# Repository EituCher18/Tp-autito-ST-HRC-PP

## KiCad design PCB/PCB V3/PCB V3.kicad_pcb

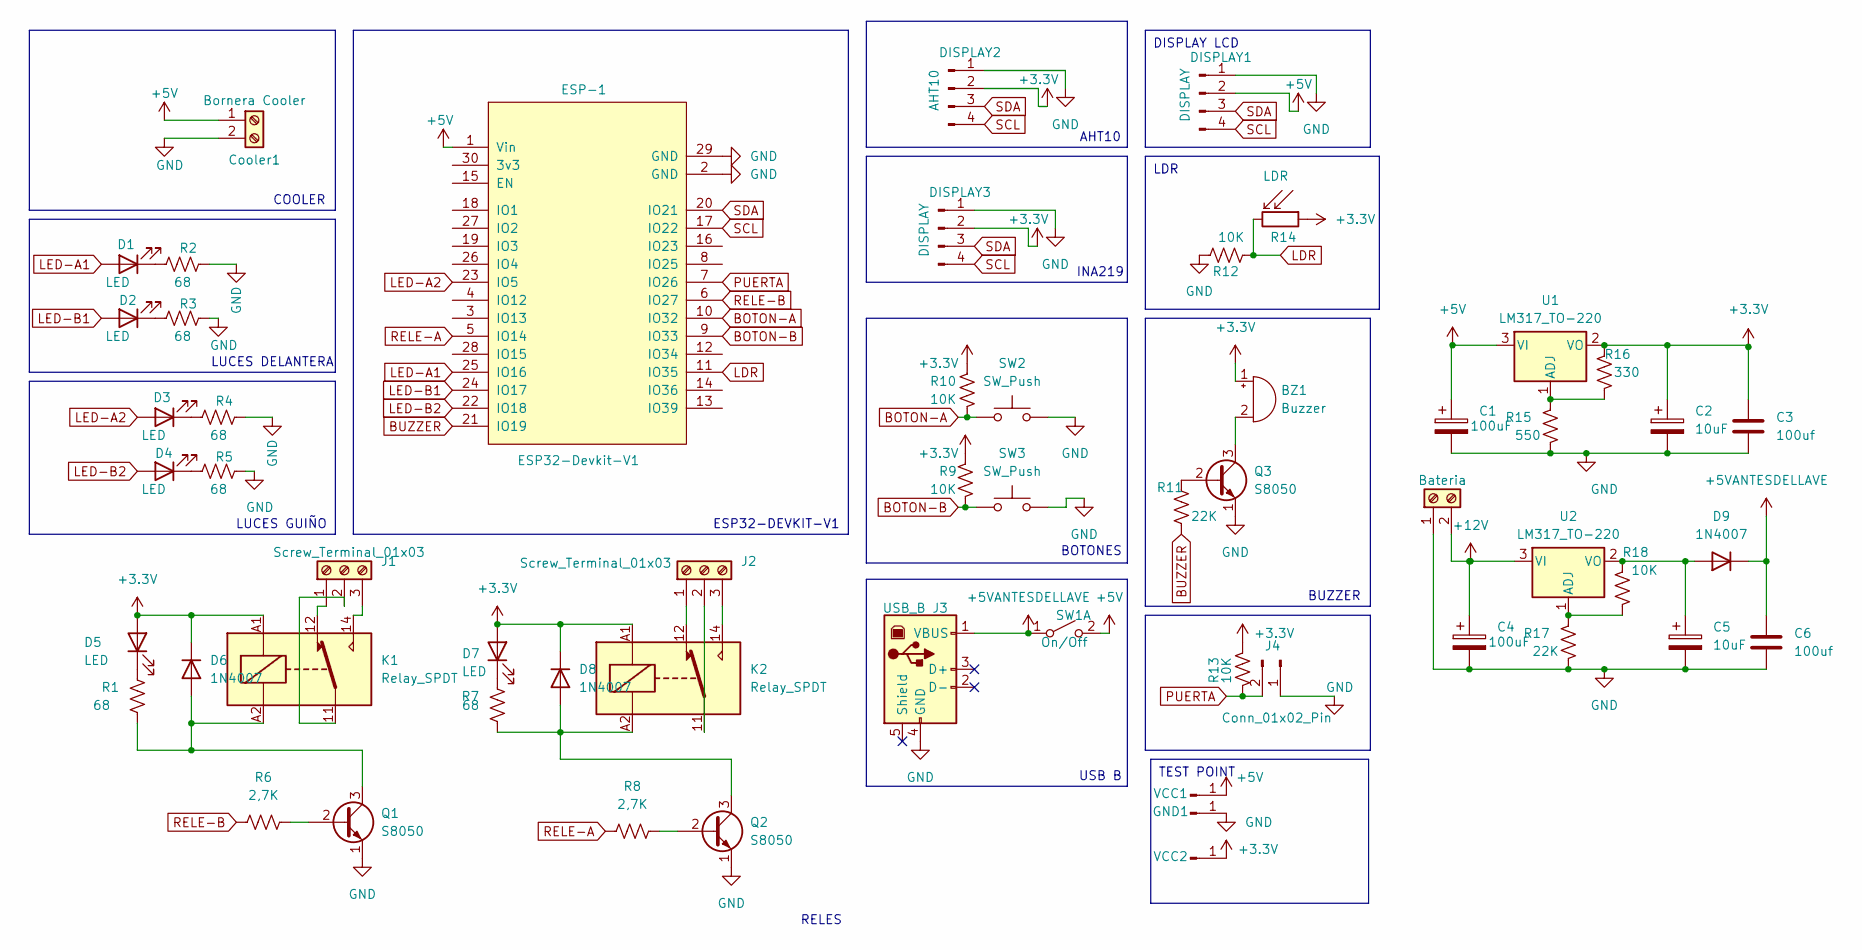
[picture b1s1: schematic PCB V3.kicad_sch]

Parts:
BZ1: Buzzer; Buzzer_12x9.5RM7.6
C1, C4: 100uF; CP_Radial_D6.3mm_P2.50mm
C2, C5: 10uF; CP_Radial_D5.0mm_P2.50mm
C3, C6: 100uf; C_Disc_D7.5mm_W4.4mm_P5.00mm
Cooler1: Bornera Cooler; TerminalBlock_bornier-2_P5.08mm
Cooler2: Bateria; TerminalBlock_bornier-2_P5.08mm
D1, D2, D3, D4: LED; Molex_KK-254_AE-6410-02A_1x02_P2.54mm_Vertical
D5, D7: LED; LED_D5.0mm_Clear
D6, D8, D9: 1N4007; D_DO-41_SOD81_P10.16mm_Horizontal
DISPLAY1, DISPLAY3: DISPLAY; Molex_KK-254_AE-6410-04A_1x04_P2.54mm_Vertical
DISPLAY2: AHT10; Molex_KK-254_AE-6410-04A_1x04_P2.54mm_Vertical
ESP-1: ESP32-Devkit-V1; DOIT_ESP32_Devkit_mirko
GND1: Conn_01x01_Pin; PinHeader_1x01_P2.54mm_Vertical
J1, J2: Screw_Terminal_01x03; TerminalBlock_bornier-3_P5.08mm
J3: USB_B; USB_B_OST_USB-B1HSxx_Horizontal
J4: Conn_01x02_Pin; Molex_KK-254_AE-6410-02A_1x02_P2.54mm_Vertical
K1, K2: Relay_SPDT; Relay_SPDT_Finder_36.11
Q1, Q2, Q3: S8050; TO-92_Inline
R1, R2, R3, R4, R5, R7: 68; R_Axial_DIN0207_L6.3mm_D2.5mm_P10.16mm_Horizontal
R6, R8: 2,7K; R_Axial_DIN0207_L6.3mm_D2.5mm_P10.16mm_Horizontal
R9, R10, R12, R13, R18: 10K; R_Axial_DIN0207_L6.3mm_D2.5mm_P10.16mm_Horizontal
R11, R17: 22K; R_Axial_DIN0207_L6.3mm_D2.5mm_P10.16mm_Horizontal
R14: LDR; Molex_KK-254_AE-6410-02A_1x02_P2.54mm_Vertical
R15: 550; R_Axial_DIN0207_L6.3mm_D2.5mm_P10.16mm_Horizontal
R16: 330; R_Axial_DIN0207_L6.3mm_D2.5mm_P10.16mm_Horizontal
SW1: On/Off; TerminalBlock_bornier-2_P5.08mm
SW2, SW3: SW_Push; Molex_KK-254_AE-6410-02A_1x02_P2.54mm_Vertical
U1, U2: LM317_TO-220; TO-220-3_Vertical
VCC1, VCC2: Conn_01x01_Pin; PinHeader_1x01_P2.54mm_Vertical

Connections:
+3.3V: BZ1.1 (+), C2.1, C3.1, D5.2 (A), D6.1 (K), D7.2 (A), D8.1 (K), DISPLAY2.2, DISPLAY3.2, K1.A1, K2.A1, R9.1, R10.1, R13.1, R14.1, R16.2, U1.2 (VO), VCC2.1
+5V: C1.1, Cooler1.1, DISPLAY1.2, ESP-1.1 (Vin), SW1.2 (B), U1.3 (VI), VCC1.1
+5VANTESDELLAVE: C6.1, D9.1 (K), J3.1 (VBUS), SW1.1 (A)
+12V: C4.1, Cooler2.2, U2.3 (VI)
BOTON-A: ESP-1.10 (IO32), R10.2, SW2.1
BOTON-B: ESP-1.9 (IO33), R9.2, SW3.1
BUZZER: ESP-1.21 (IO19), R11.2
GND: C1.2, C2.2, C3.2, C4.2, C5.2, C6.2, Cooler1.2, Cooler2.1, DISPLAY1.1, DISPLAY2.1, DISPLAY3.1, ESP-1.2 (GND), ESP-1.29 (GND), GND1.1, J3.4 (GND), J4.1, Q1.1 (E), Q2.1 (E), Q3.1 (E), R2.1, R3.1, R4.1, R5.1, R12.2, R15.2, R17.2, SW2.2, SW3.2
LDR: ESP-1.11 (IO35), R12.1, R14.2
LED-A1: D1.2 (A), ESP-1.25 (IO16)
LED-A2: D3.2 (A), ESP-1.23 (IO5)
LED-B1: D2.2 (A), ESP-1.24 (IO17)
LED-B2: D4.2 (A), ESP-1.22 (IO18)
unnamed: BZ1.2 (-), Q3.3 (C)
unnamed: D1.1 (K), R2.2
unnamed: D2.1 (K), R3.2
unnamed: D3.1 (K), R4.2
unnamed: D4.1 (K), R5.2
unnamed: D5.1 (K), R1.1
unnamed: D6.2 (A), K1.A2, Q1.3 (C), R1.2
unnamed: D7.1 (K), R7.1
unnamed: D8.2 (A), K2.A2, Q2.3 (C), R7.2
unnamed: C5.1, D9.2 (A), R18.2, U2.2 (VO)
unnamed: J1.1, K1.12
unnamed: J1.2, K1.11
unnamed: J1.3, K1.14
unnamed: J2.1, K2.12
unnamed: J2.2, K2.11
unnamed: J2.3, K2.14
unnamed: Q1.2 (B), R6.2
unnamed: Q2.2 (B), R8.2
unnamed: Q3.2 (B), R11.1
unnamed: R15.1, R16.1, U1.1 (ADJ)
unnamed: R17.1, R18.1, U2.1 (ADJ)
PUERTA: ESP-1.7 (IO26), J4.2, R13.2
RELE-A: ESP-1.5 (IO14), R8.1
RELE-B: ESP-1.6 (IO27), R6.1
SCL: DISPLAY1.4, DISPLAY2.4, DISPLAY3.4, ESP-1.17 (IO22)
SDA: DISPLAY1.3, DISPLAY2.3, DISPLAY3.3, ESP-1.20 (IO21)

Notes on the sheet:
TEST POINT
LDR
DISPLAY LCD
INA219
LUCES DELANTERA
LUCES GUIÑO
ESP32-DEVKIT-V1
RELES
USB B
COOLER
BOTONES
BUZZER
AHT10

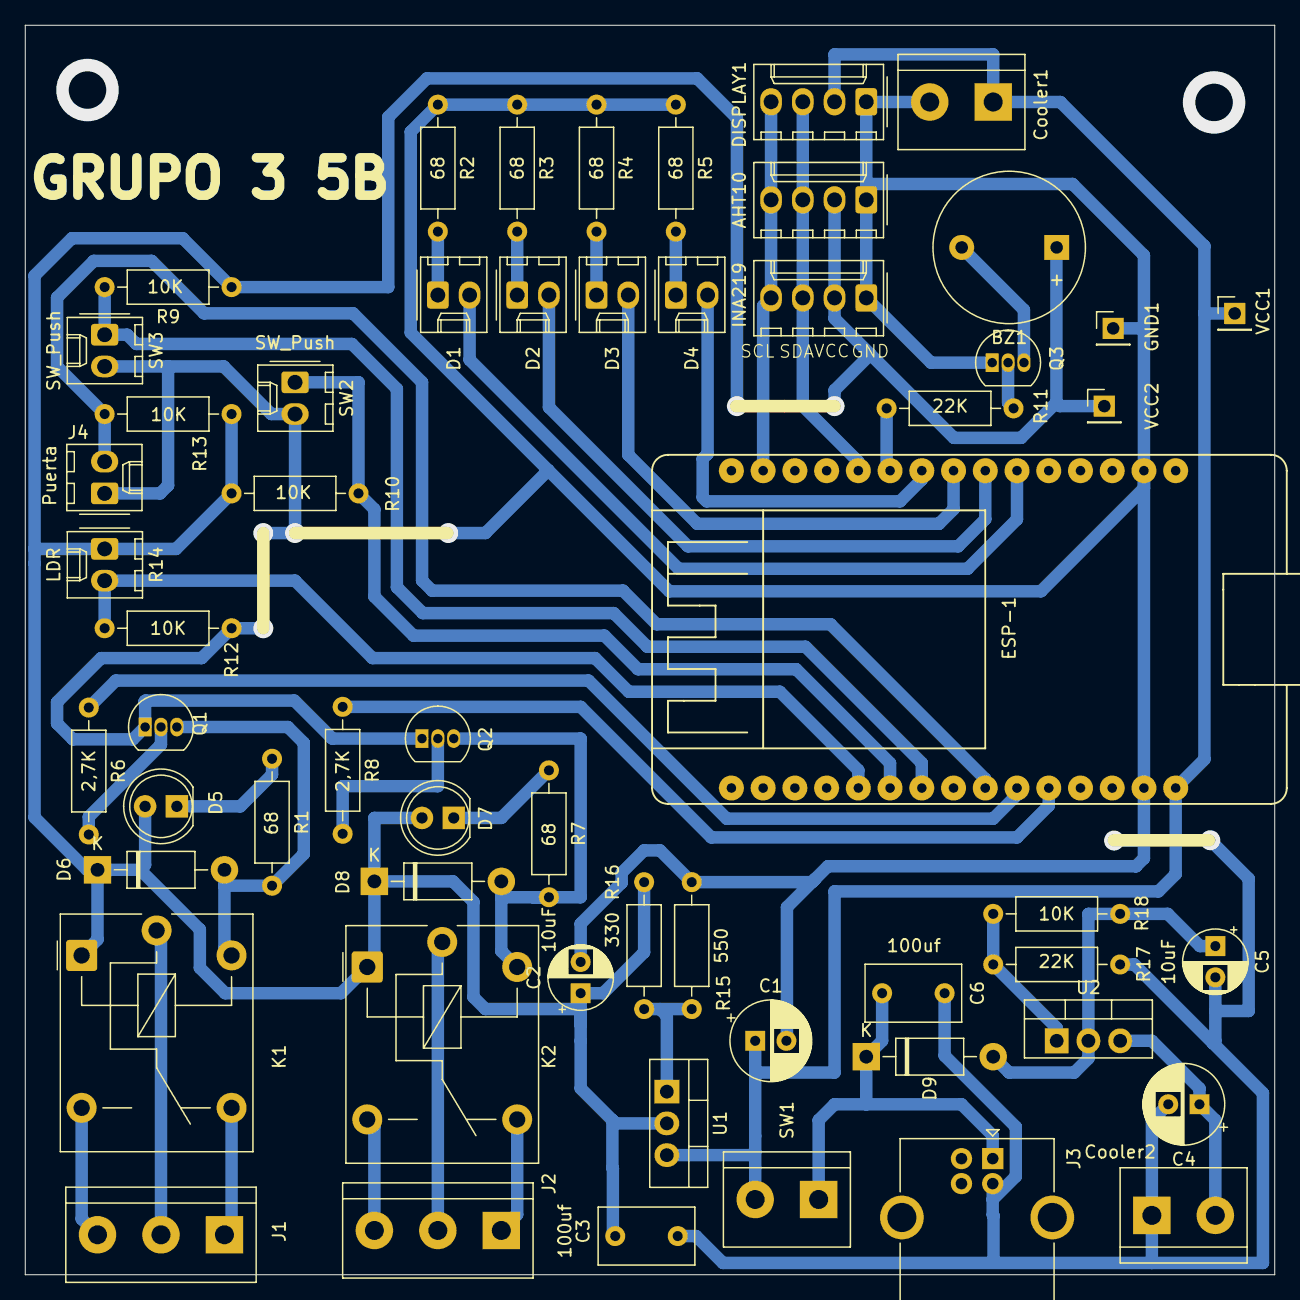
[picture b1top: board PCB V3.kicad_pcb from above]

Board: 2 copper layers, 100.0 x 100.0 mm, 57 parts (0 on the bottom side), 39 nets.

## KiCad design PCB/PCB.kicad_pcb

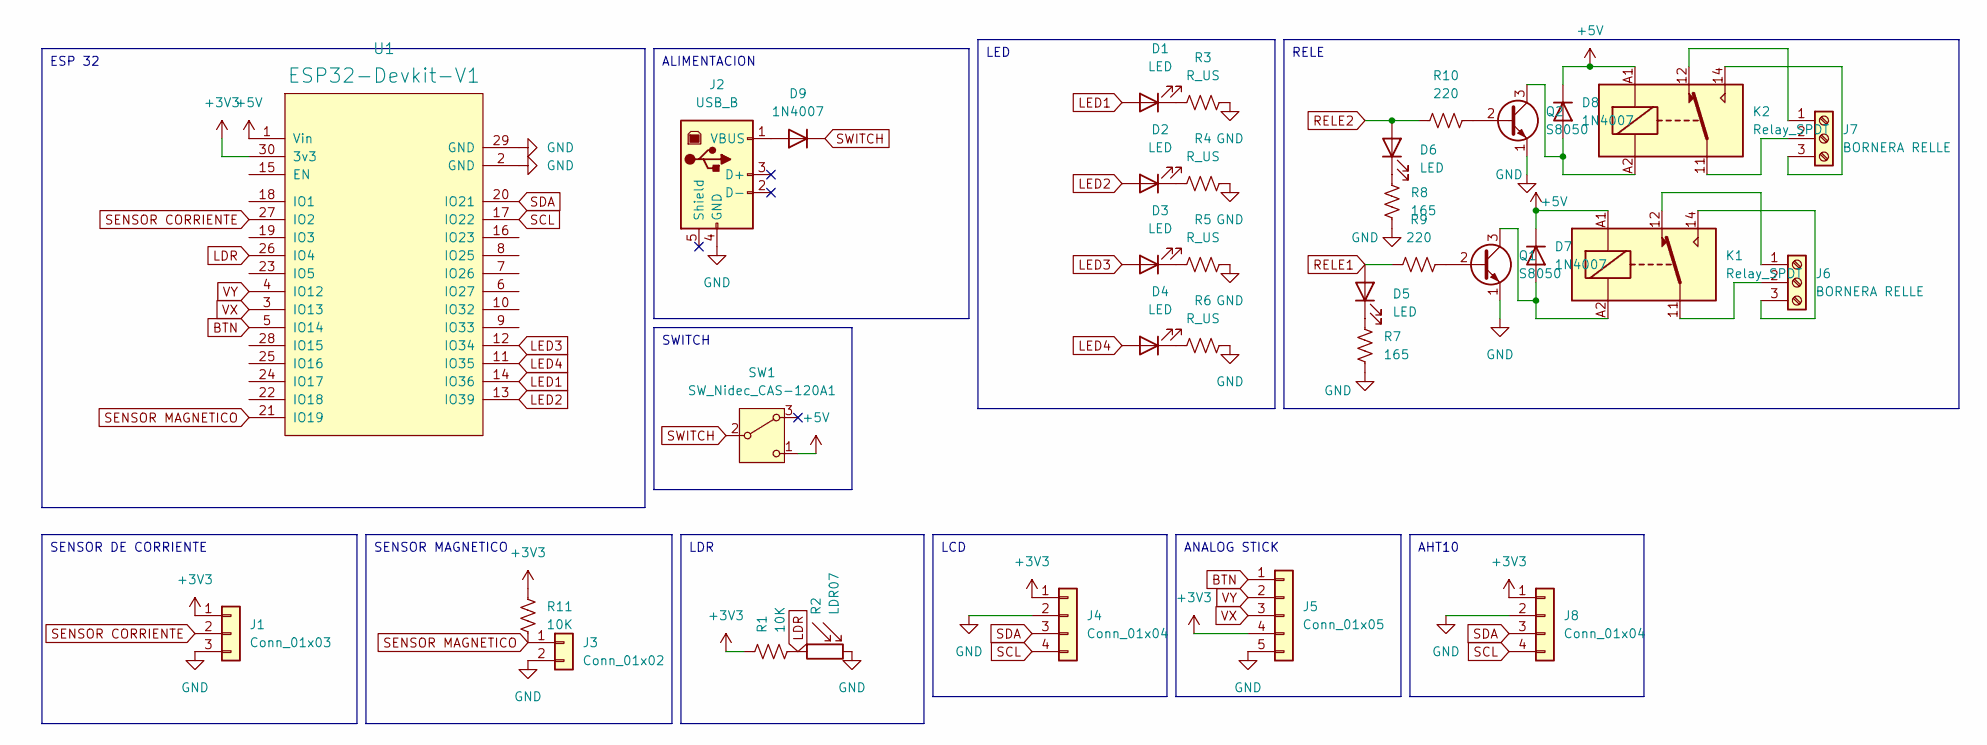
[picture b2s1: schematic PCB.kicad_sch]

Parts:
D1, D2, D3, D4: LED; Molex_KK-254_AE-6410-02A_1x02_P2.54mm_Vertical
D5, D6: LED; LED_D5.0mm
D7, D8, D9: 1N4007; D_DO-41_SOD81_P10.16mm_Horizontal
J1: Conn_01x03; Molex_KK-254_AE-6410-03A_1x03_P2.54mm_Vertical
J2: USB_B; USB_B_OST_USB-B1HSxx_Horizontal
J3: Conn_01x02; Molex_KK-254_AE-6410-02A_1x02_P2.54mm_Vertical
J4, J8: Conn_01x04; Molex_KK-254_AE-6410-04A_1x04_P2.54mm_Vertical
J5: Conn_01x05; Molex_KK-254_AE-6410-05A_1x05_P2.54mm_Vertical
J6, J7: BORNERA RELLE; TerminalBlock_Phoenix_MKDS-1,5-3-5.08_1x03_P5.08mm_Horizont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
K1, K2: Relay_SPDT; Relay_SPDT_Finder_36.11
Q1, Q2: S8050; TO-92_Inline
R1, R11: 10K; R_Axial_DIN0207_L6.3mm_D2.5mm_P10.16mm_Horizontal
R2: LDR07; Molex_KK-254_AE-6410-02A_1x02_P2.54mm_Vertical
R3, R4, R5, R6: R_US; R_Axial_DIN0207_L6.3mm_D2.5mm_P10.16mm_Horizontal
R7, R8: 165; R_Axial_DIN0207_L6.3mm_D2.5mm_P10.16mm_Horizontal
R9, R10: 220; R_Axial_DIN0207_L6.3mm_D2.5mm_P10.16mm_Horizontal
SW1: SW_Nidec_CAS-120A1; SW_Slide_SPDT_Straight_CK_OS102011MS2Q
U1: ESP32-Devkit-V1; DOIT_ESP32_Devkit_mirko

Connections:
+3V3: J1.1, J4.1, J5.4, J8.1, R1.2, R11.1, U1.30 (3v3)
+5V: D7.1 (K), D8.1 (K), K1.A1, K2.A1, SW1.1 (C), U1.1 (Vin)
BTN: J5.1, U1.5 (IO14)
GND: J1.3, J2.4 (GND), J3.2, J4.2, J5.5, J8.2, Q1.1 (E), Q2.1 (E), R2.2, R3.2, R4.2, R5.2, R6.2, R7.1, R8.1, U1.2 (GND), U1.29 (GND)
LDR: R1.1, R2.1, U1.26 (IO4)
LED1: D1.2 (A), U1.14 (IO36)
LED2: D2.2 (A), U1.13 (IO39)
LED3: D3.2 (A), U1.12 (IO34)
LED4: D4.2 (A), U1.11 (IO35)
unnamed: D1.1 (K), R3.1
unnamed: D2.1 (K), R4.1
unnamed: D3.1 (K), R5.1
unnamed: D4.1 (K), R6.1
unnamed: D5.1 (K), R7.2
unnamed: D6.1 (K), R8.2
unnamed: D7.2 (A), K1.A2, Q1.3 (C)
unnamed: D8.2 (A), K2.A2, Q2.3 (C)
unnamed: D9.2 (A), J2.1 (VBUS)
unnamed: J6.1, K1.12
unnamed: J6.2, K1.11
unnamed: J6.3, K1.14
unnamed: J7.1, K2.12
unnamed: J7.2, K2.11
unnamed: J7.3, K2.14
unnamed: Q1.2 (B), R9.1
unnamed: Q2.2 (B), R10.1
RELE1: D5.2 (A), R9.2
RELE2: D6.2 (A), R10.2
SCL: J4.4, J8.4, U1.17 (IO22)
SDA: J4.3, J8.3, U1.20 (IO21)
SENSOR CORRIENTE: J1.2, U1.27 (IO2)
SENSOR MAGNETICO: J3.1, R11.2, U1.21 (IO19)
SWITCH: D9.1 (K), SW1.2 (B)
VX: J5.3, U1.3 (IO13)
VY: J5.2, U1.4 (IO12)

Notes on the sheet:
SWITCH
ESP 32
ALIMENTACION
LED
SENSOR MAGNETICO
SENSOR DE CORRIENTE
LDR
RELE
AHT10
ANALOG STICK
LCD

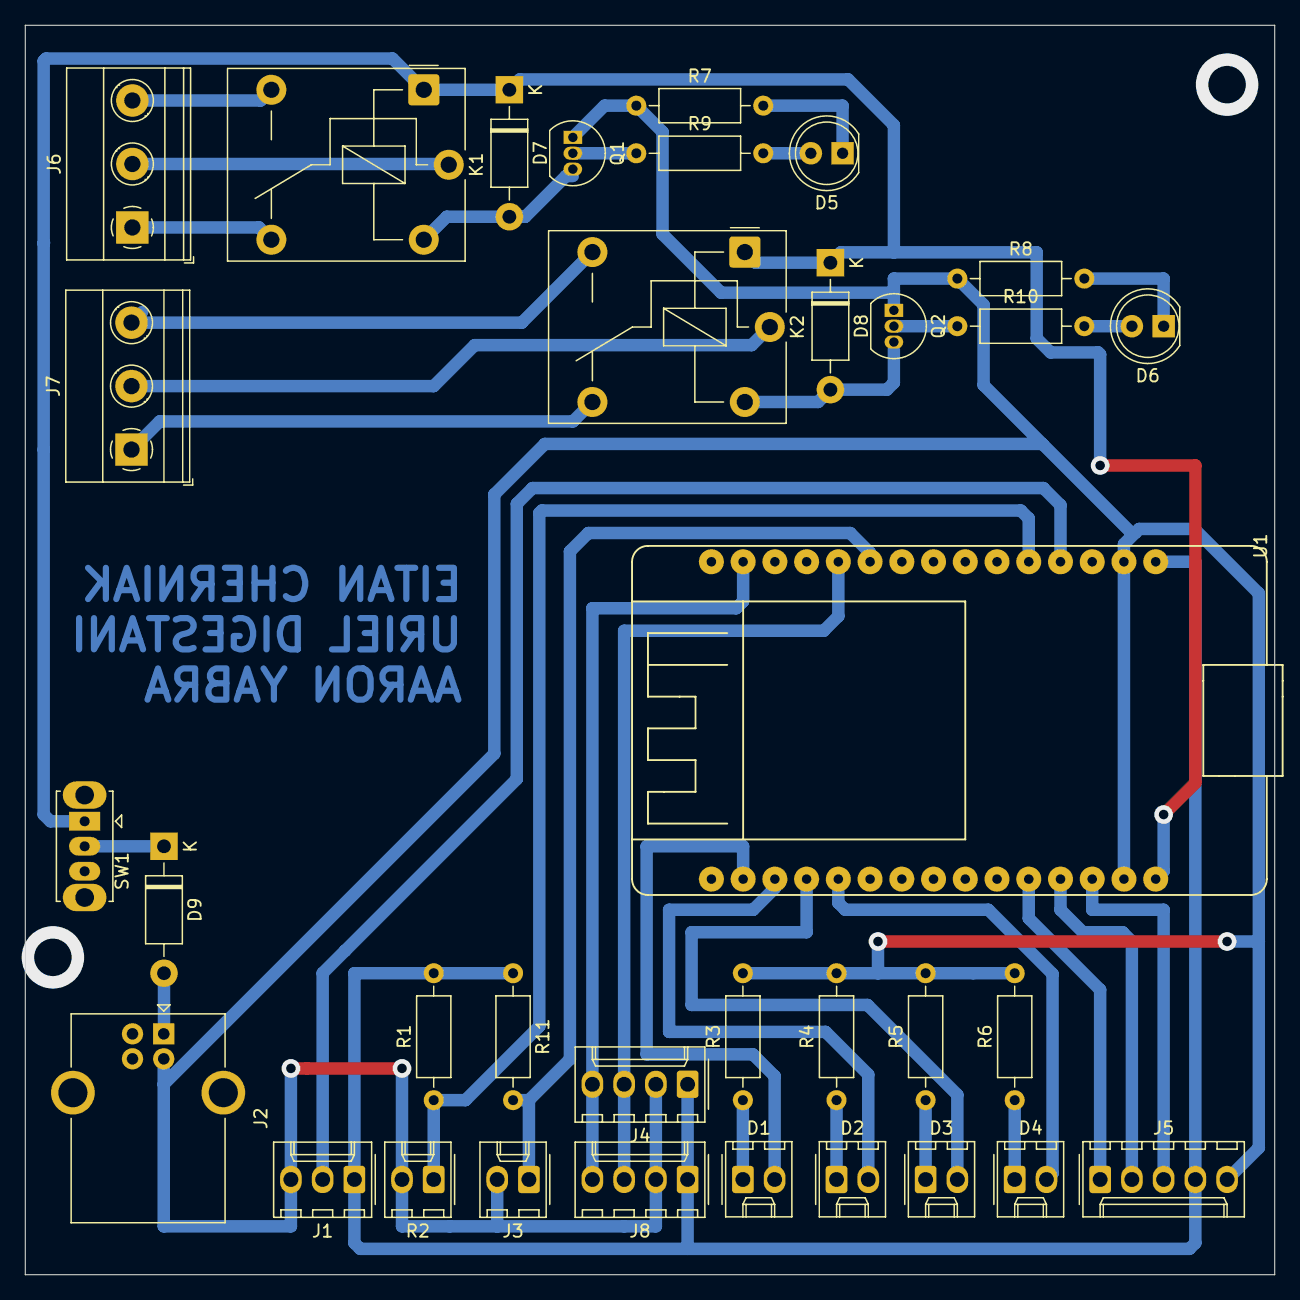
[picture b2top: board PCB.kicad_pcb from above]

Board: 2 copper layers, 100.0 x 100.0 mm, 34 parts (0 on the bottom side), 35 nets.

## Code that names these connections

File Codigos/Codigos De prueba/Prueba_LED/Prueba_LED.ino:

#define Led1
#define Led2 
#define Led3
#define Led4
void setup() {
pinMode(Led1, OUTPUT);
pinMode(Led2, OUTPUT);
pinMode(Led3, OUTPUT);
pinMode(Led4, OUTPUT);
}

void loop() {
digitalWrite(Led1, HIGH);
digitalWrite(Led2, HIGH);
digitalWrite(Led3, HIGH);
digitalWrite(Led4, HIGH);
delay(1000);
digitalWrite(Led1, LOW);
digitalWrite(Led2, LOW);
digitalWrite(Led3, LOW);
digitalWrite(Led4, LOW);
delay(1000);
}

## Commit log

2024-09-16 Codigos de prueba
2024-10-14 No compila
2024-10-15 Falta buzzer telegram
2024-10-15 Borrar las cosas que falta
2024-10-18 Colocar WIFI
2024-10-24 Agregue Umbral de temperatura y su pantalla de modiicaion y su estado intermedio
2024-11-12 V2 Falta cambiar fotprint de los capacitores y agregar bornera de INA219
2024-11-13 Cambiado el footprint del capacitor
2024-12-05 PCB V3
